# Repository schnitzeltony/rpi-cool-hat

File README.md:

# rpi-cool-hat

* At least Raspberry Pi 4 makes additional cooling mandatory.
* Most cooling solutions (all but oil?) do not allow stacked HATs (and at least musicians do not accept built-in audio).

This KiCad project suggests a glue-PCB letting coolers and HATs live in peace:

RPi is connected left / HAT connected right / cooler's fan connected to pins in the back as (example pictures are 180°rotated):

**Note that the project:**

* was created by Kicad 5.1.5 as shipped by Fedora 30
* 's author is not a professional layouter - awaiting PRs/issues - teach me :grin:
* was tested with HifiBerry DAC Pro and Flatmax AudioInjector
* IS PROVIDED "AS IS", WITHOUT WARRANTY OF ANY KIND!

**If you want one:**

* drop [rpi-cool-hat.kicad_pcb](rpi-cool-hat.kicad_pcb) to a supplier of your choice
* if your supplier does not accept Kicad: clone this project, go through gerber and send that to your supplier.
  To get an idea of how to accomplish it might help to watch https://www.youtube.com/watch?v=ENmDnoKs2hM
* or visit https://aisler.net/p/IRBRWUAC. Note that the author has no relation to Aisler.
  It was chosen because their production was considered close at time and place of writing.

**Tips:**

* Start soldering with J1
* When using Ice Tower Cooler cables are a bit short. To get around: Unmount fan, rotate 90° clockwise and mount again. Be careful not to over-tighten screws!
* For Ice Tower Cooler noise can be reduced significantly by using 3.3V supply on J1 (as written in the handbook). With reduced voltage I never saw CPU temperature rising above 45°
* If space is limited one might want to use a 90° variant of J2:

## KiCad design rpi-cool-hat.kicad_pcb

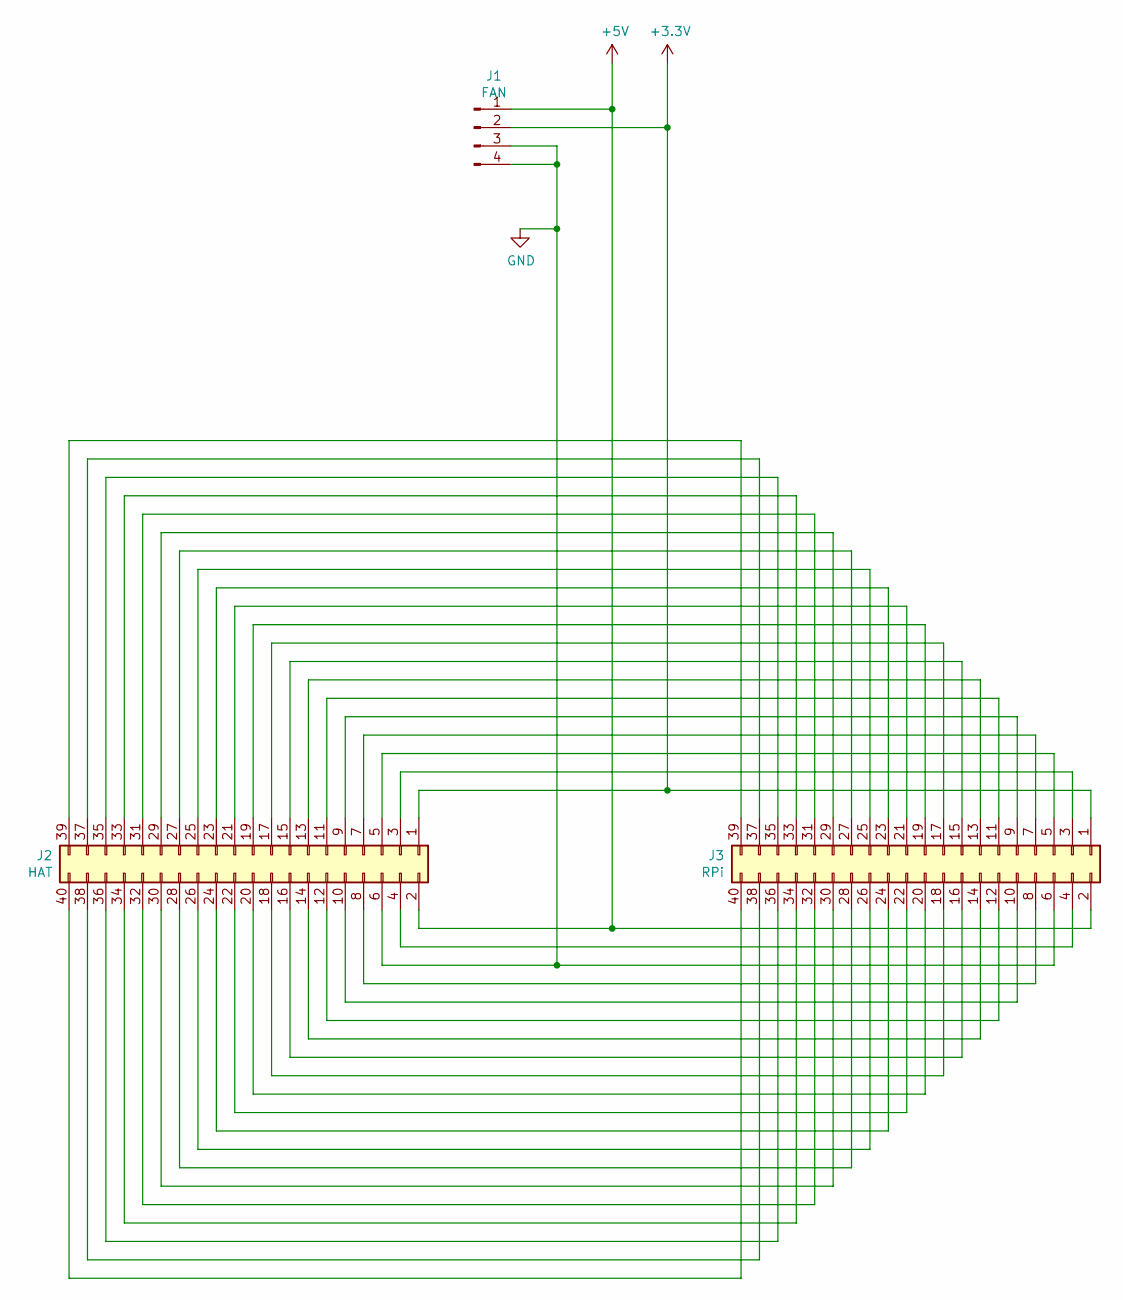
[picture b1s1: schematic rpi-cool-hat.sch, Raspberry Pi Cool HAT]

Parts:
J1: FAN; PinHeader_1x04_P2.54mm_Vertical
J2: HAT; PinHeader_2x20_P2.54mm_Vertical
J3: RPi; PinSocket_2x20_P2.54mm_Vertical

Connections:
+3V3: J1.2, J2.1, J3.1
+5V: J1.1, J2.2, J3.2
GND: J1.3, J1.4, J2.6, J3.6
unnamed: J2.3, J3.3
unnamed: J2.4, J3.4
unnamed: J2.5, J3.5
unnamed: J2.7, J3.7
unnamed: J2.8, J3.8
unnamed: J2.9, J3.9
unnamed: J2.10, J3.10
unnamed: J2.11, J3.11
unnamed: J2.12, J3.12
unnamed: J2.13, J3.13
unnamed: J2.14, J3.14
unnamed: J2.15, J3.15
unnamed: J2.16, J3.16
unnamed: J2.17, J3.17
unnamed: J2.18, J3.18
unnamed: J2.19, J3.19
unnamed: J2.20, J3.20
unnamed: J2.21, J3.21
unnamed: J2.22, J3.22
unnamed: J2.23, J3.23
unnamed: J2.24, J3.24
unnamed: J2.25, J3.25
unnamed: J2.26, J3.26
unnamed: J2.27, J3.27
unnamed: J2.28, J3.28
unnamed: J2.29, J3.29
unnamed: J2.30, J3.30
unnamed: J2.31, J3.31
unnamed: J2.32, J3.32
unnamed: J2.33, J3.33
unnamed: J2.34, J3.34
unnamed: J2.35, J3.35
unnamed: J2.36, J3.36
unnamed: J2.37, J3.37
unnamed: J2.38, J3.38
unnamed: J2.39, J3.39
unnamed: J2.40, J3.40

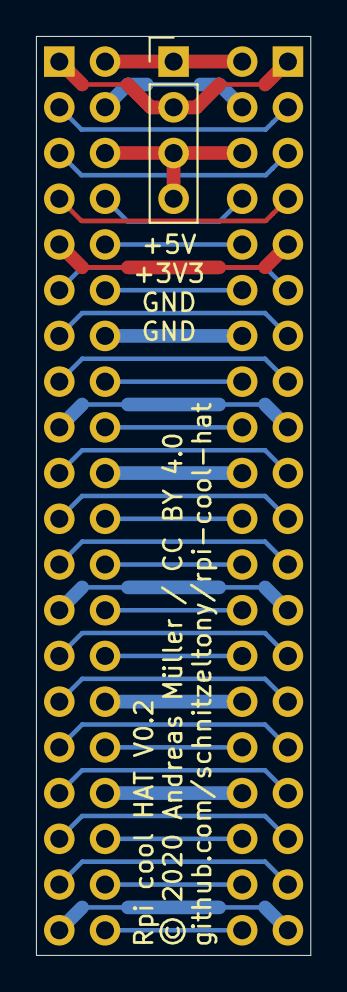
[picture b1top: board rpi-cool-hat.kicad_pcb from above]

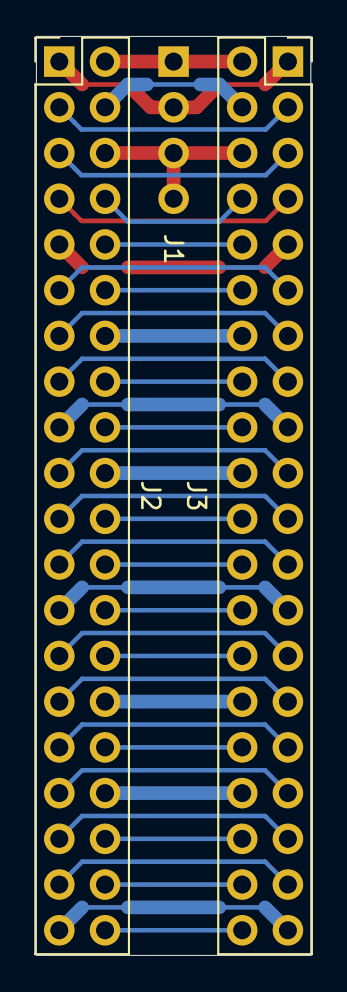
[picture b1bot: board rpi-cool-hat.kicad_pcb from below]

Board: 2 copper layers, 15.2 x 51.1 mm, 3 parts (2 on the bottom side), 40 nets.

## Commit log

2019-12-21 Thicken 5V @ pin 4
2019-12-21 Rework Power/GND lines
2019-12-21 Add a tiny README
2019-12-22 Readme-rework
2019-12-22 PCB: minor fine tuning on lables and board dimension
2019-12-22 .gitignore: add autosave files
2019-12-22 gitignore: add *.zip
2019-12-22 PCB Show all layers
2019-12-22 README.md: add shared order information
2019-12-22 README.md: raytraced 3D is more pretty
2019-12-22 README: try to explain where to get and what it's about
2019-12-23 README: fix whateverko
2019-12-23 more README
2019-12-23 even more README
2019-12-23 guess what: README
2019-12-23 README
2019-12-23 README
    was close to amend...
2020-01-01 README: Cleanup lower part explaining how to get one
2020-01-05 README.md: spelling
2020-02-17 PCB: rework
    * Got puzzled with let and right. That caused fan connector pins connected at
    wrong pins.
    * Used 50mils for routing which caused cleaner layout
    * Reduced PCB size
2020-02-24 README.md: Now that we tested it's time for more text and pictures
2020-02-24 README.md: Fix typo
2020-11-13 Add fp-info-cache to .gitignore
2020-11-13 Revert "Add fp-info-cache to .gitignore"
    This reverts commit ec17ddb642db0f5cbaea6720320e5e15c0b29bfd.
2020-11-13 remove fp-info-cache
2021-07-15 README.md: Fix upside down initial thinko
2021-07-16 Minor proposals (lines 04, 34)

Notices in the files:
rpi-cool-hat.kicad_pcb:
License CC BY 4.0
© 2020 Andreas Müller / CC BY 4.0
rpi-cool-hat.sch:
creativecommons.org/licenses/by/4.0
